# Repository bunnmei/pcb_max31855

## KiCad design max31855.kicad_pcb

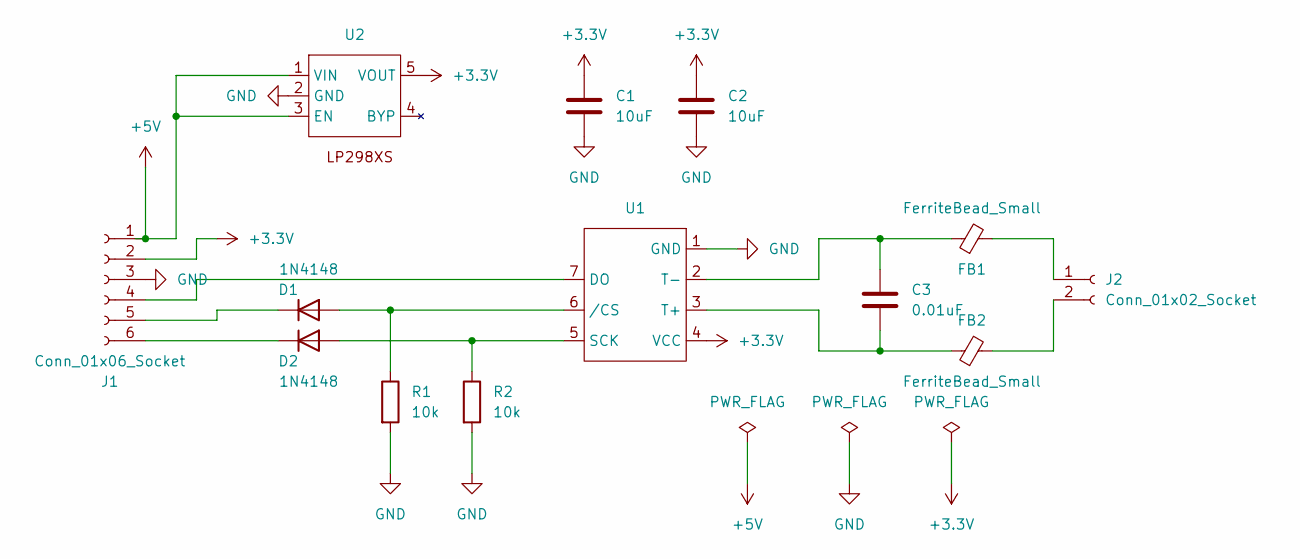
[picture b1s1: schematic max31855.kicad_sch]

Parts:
C1, C2: 10uF; C_0603_1608Metric
C3: 0.01uF; C_0603_1608Metric
D1, D2: 1N4148; D_0603_1608Metric
FB1, FB2: FerriteBead_Small; C_0603_1608Metric
J1: Conn_01x06_Socket; PinSocket_1x06_P2.54mm_Vertical
J2: Conn_01x02_Socket; PinSocket_1x02_P2.00mm_Vertical
R1, R2: 10k; R_0603_1608Metric
U1: SOIC-8_3.9x4.9mm_P1.27mm
U2: LP298XS

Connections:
+3.3V: C1.1, C2.1, J1.2, U1.4 (VCC), U2.5 (VOUT)
+5V: J1.1, U2.1 (VIN), U2.3 (EN)
GND: C1.2, C2.2, J1.3, R1.2, R2.2, U1.1 (GND), U2.2 (GND)
unnamed: D1.2 (A), R1.1, U1.6 (/CS)
unnamed: D1.1 (K), J1.5
unnamed: D2.2 (A), R2.1, U1.5 (SCK)
unnamed: D2.1 (K), J1.6
unnamed: J1.4, U1.7 (DO)
unnamed: FB1.2, J2.1
unnamed: FB2.2, J2.2
unnamed: C3.2, FB2.1, U1.3 (T+)
unnamed: C3.1, FB1.1, U1.2 (T-)

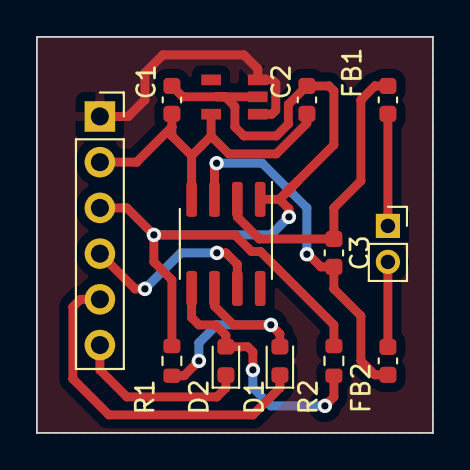
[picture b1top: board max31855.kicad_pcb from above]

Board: 2 copper layers, 22.0 x 22.0 mm, 13 parts (0 on the bottom side), 12 nets.

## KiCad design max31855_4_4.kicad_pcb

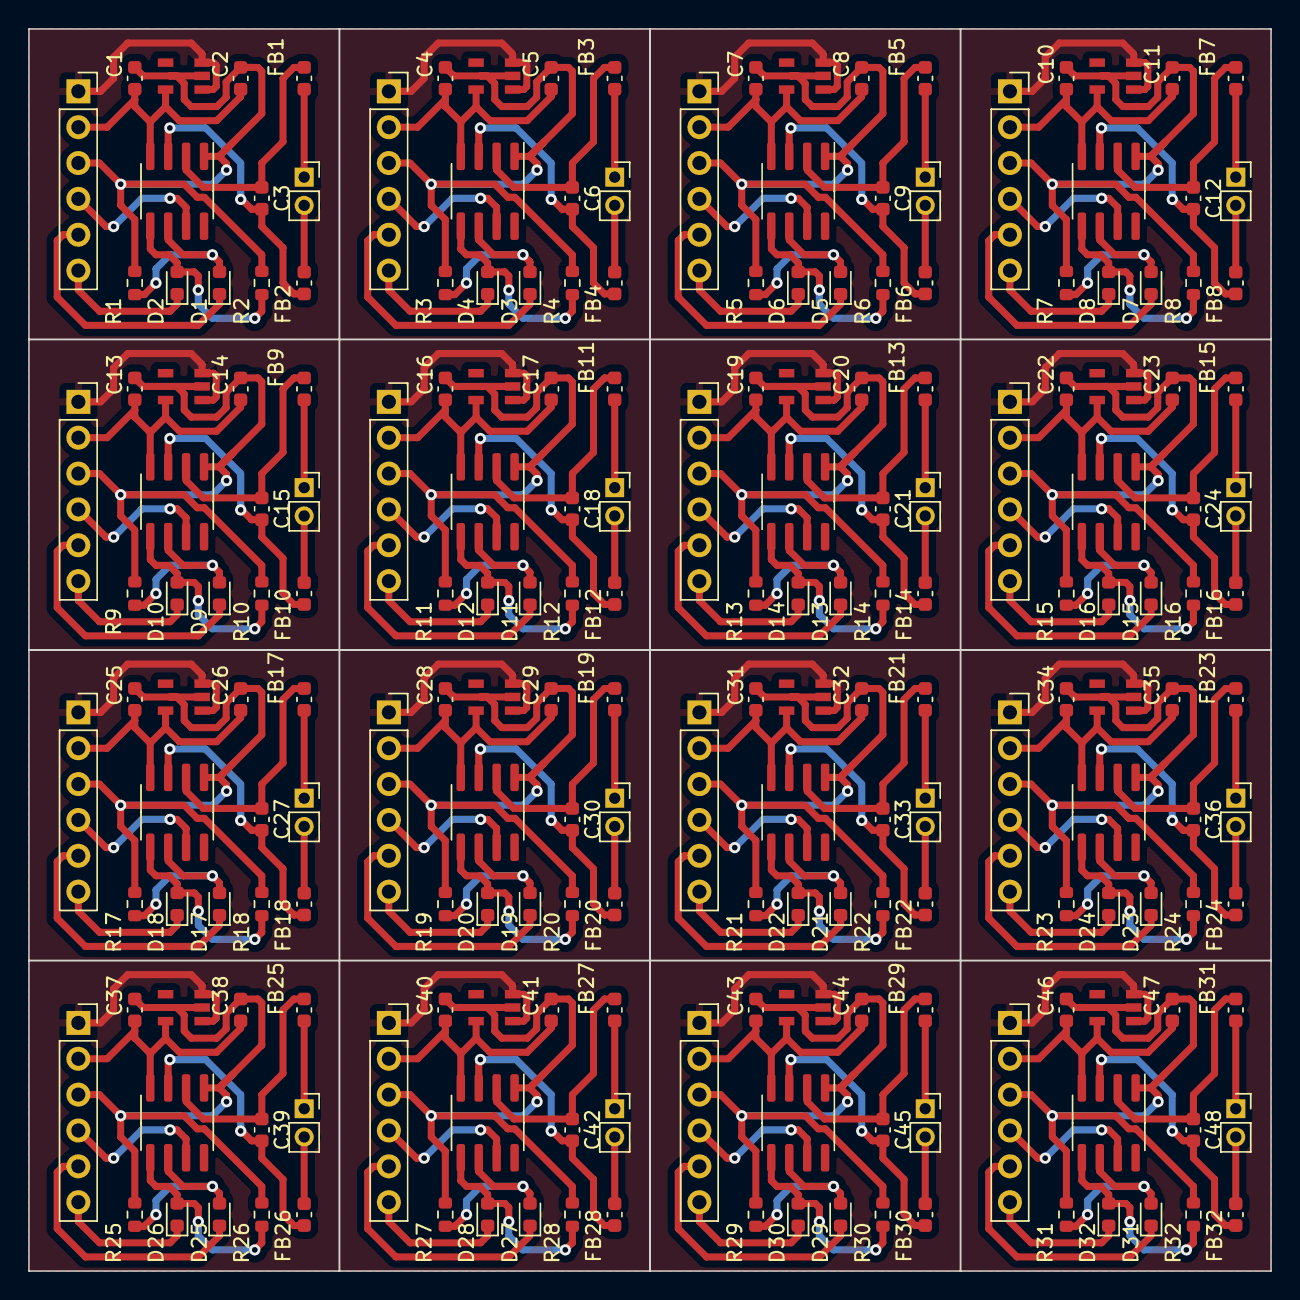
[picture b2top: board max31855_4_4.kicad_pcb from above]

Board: 2 copper layers, 88.0 x 88.0 mm, 208 parts (0 on the bottom side), 12 nets.

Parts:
C1, C2, C4, C5, C7, C8, C10, C11, C13, C14, C16, C17, C19, C20, C22, C23, C25, C26, C28, C29, C31, C32, C34, C35, C37, C38, C40, C41, C43, C44, C46, C47: 10uF; C_0603_1608Metric
C3, C6, C9, C12, C15, C18, C21, C24, C27, C30, C33, C36, C39, C42, C45, C48: 0.01uF; C_0603_1608Metric
D1, D2, D3, D4, D5, D6, D7, D8, D9, D10, D11, D12, D13, D14, D15, D16, D17, D18, D19, D20, D21, D22, D23, D24, D25, D26, D27, D28, D29, D30, D31, D32: 1N4148; D_0603_1608Metric
FB1, FB2, FB3, FB4, FB5, FB6, FB7, FB8, FB9, FB10, FB11, FB12, FB13, FB14, FB15, FB16, FB17, FB18, FB19, FB20, FB21, FB22, FB23, FB24, FB25, FB26, FB27, FB28, FB29, FB30, FB31, FB32: FerriteBead_Small; C_0603_1608Metric
J1, J3, J5, J7, J9, J11, J13, J15, J17, J19, J21, J23, J25, J27, J29, J31: Conn_01x06_Socket; PinSocket_1x06_P2.54mm_Vertical
J2, J4, J6, J8, J10, J12, J14, J16, J18, J20, J22, J24, J26, J28, J30, J32: Conn_01x02_Socket; PinSocket_1x02_P2.00mm_Vertical
R1, R2, R3, R4, R5, R6, R7, R8, R9, R10, R11, R12, R13, R14, R15, R16, R17, R18, R19, R20, R21, R22, R23, R24, R25, R26, R27, R28, R29, R30, R31, R32: 10k; R_0603_1608Metric
U1, U3, U5, U7, U9, U11, U13, U15, U17, U19, U21, U23, U25, U27, U29, U31: SOIC-8_3.9x4.9mm_P1.27mm
U2, U4, U6, U8, U10, U12, U14, U16, U18, U20, U22, U24, U26, U28, U30, U32: LP298XS

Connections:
+3.3V: C1.1, C2.1, C4.1, C5.1, C7.1, C8.1, C10.1, C11.1, C13.1, C14.1, C16.1, C17.1, C19.1, C20.1, C22.1, C23.1, C25.1, C26.1, C28.1, C29.1, C31.1, C32.1, C34.1, C35.1, C37.1, C38.1, C40.1, C41.1, C43.1, C44.1, C46.1, C47.1, J1.2, J3.2, J5.2, J7.2, J9.2, J11.2, J13.2, J15.2, J17.2, J19.2, J21.2, J23.2, J25.2, J27.2, J29.2, J31.2, U1.4 (VCC), U2.5 (VOUT), U3.4 (VCC), U4.5 (VOUT), U5.4 (VCC), U6.5 (VOUT), U7.4 (VCC), U8.5 (VOUT), U9.4 (VCC), U10.5 (VOUT), U11.4 (VCC), U12.5 (VOUT), U13.4 (VCC), U14.5 (VOUT), U15.4 (VCC), U16.5 (VOUT), U17.4 (VCC), U18.5 (VOUT), U19.4 (VCC), U20.5 (VOUT), U21.4 (VCC), U22.5 (VOUT), U23.4 (VCC), U24.5 (VOUT), U25.4 (VCC), U26.5 (VOUT), U27.4 (VCC), U28.5 (VOUT), U29.4 (VCC), U30.5 (VOUT), U31.4 (VCC), U32.5 (VOUT)
+5V: J1.1, J3.1, J5.1, J7.1, J9.1, J11.1, J13.1, J15.1, J17.1, J19.1, J21.1, J23.1, J25.1, J27.1, J29.1, J31.1, U2.1 (VIN), U2.3 (EN), U4.1 (VIN), U4.3 (EN), U6.1 (VIN), U6.3 (EN), U8.1 (VIN), U8.3 (EN), U10.1 (VIN), U10.3 (EN), U12.1 (VIN), U12.3 (EN), U14.1 (VIN), U14.3 (EN), U16.1 (VIN), U16.3 (EN), U18.1 (VIN), U18.3 (EN), U20.1 (VIN), U20.3 (EN), U22.1 (VIN), U22.3 (EN), U24.1 (VIN), U24.3 (EN), U26.1 (VIN), U26.3 (EN), U28.1 (VIN), U28.3 (EN), U30.1 (VIN), U30.3 (EN), U32.1 (VIN), U32.3 (EN)
GND: C1.2, C2.2, C4.2, C5.2, C7.2, C8.2, C10.2, C11.2, C13.2, C14.2, C16.2, C17.2, C19.2, C20.2, C22.2, C23.2, C25.2, C26.2, C28.2, C29.2, C31.2, C32.2, C34.2, C35.2, C37.2, C38.2, C40.2, C41.2, C43.2, C44.2, C46.2, C47.2, J1.3, J3.3, J5.3, J7.3, J9.3, J11.3, J13.3, J15.3, J17.3, J19.3, J21.3, J23.3, J25.3, J27.3, J29.3, J31.3, R1.2, R2.2, R3.2, R4.2, R5.2, R6.2, R7.2, R8.2, R9.2, R10.2, R11.2, R12.2, R13.2, R14.2, R15.2, R16.2, R17.2, R18.2, R19.2, R20.2, R21.2, R22.2, R23.2, R24.2, R25.2, R26.2, R27.2, R28.2, R29.2, R30.2, R31.2, R32.2, U1.1 (GND), U2.2 (GND), U3.1 (GND), U4.2 (GND), U5.1 (GND), U6.2 (GND), U7.1 (GND), U8.2 (GND), U9.1 (GND), U10.2 (GND), U11.1 (GND), U12.2 (GND), U13.1 (GND), U14.2 (GND), U15.1 (GND), U16.2 (GND), U17.1 (GND), U18.2 (GND), U19.1 (GND), U20.2 (GND), U21.1 (GND), U22.2 (GND), U23.1 (GND), U24.2 (GND), U25.1 (GND), U26.2 (GND), U27.1 (GND), U28.2 (GND), U29.1 (GND), U30.2 (GND), U31.1 (GND), U32.2 (GND)
unnamed: D1.2 (A), D3.2 (A), D5.2 (A), D7.2 (A), D9.2 (A), D11.2 (A), D13.2 (A), D15.2 (A), D17.2 (A), D19.2 (A), D21.2 (A), D23.2 (A), D25.2 (A), D27.2 (A), D29.2 (A), D31.2 (A), R1.1, R3.1, R5.1, R7.1, R9.1, R11.1, R13.1, R15.1, R17.1, R19.1, R21.1, R23.1, R25.1, R27.1, R29.1, R31.1, U1.6 (/CS), U3.6 (/CS), U5.6 (/CS), U7.6 (/CS), U9.6 (/CS), U11.6 (/CS), U13.6 (/CS), U15.6 (/CS), U17.6 (/CS), U19.6 (/CS), U21.6 (/CS), U23.6 (/CS), U25.6 (/CS), U27.6 (/CS), U29.6 (/CS), U31.6 (/CS)
unnamed: D1.1 (K), D3.1 (K), D5.1 (K), D7.1 (K), D9.1 (K), D11.1 (K), D13.1 (K), D15.1 (K), D17.1 (K), D19.1 (K), D21.1 (K), D23.1 (K), D25.1 (K), D27.1 (K), D29.1 (K), D31.1 (K), J1.5, J3.5, J5.5, J7.5, J9.5, J11.5, J13.5, J15.5, J17.5, J19.5, J21.5, J23.5, J25.5, J27.5, J29.5, J31.5
unnamed: D2.2 (A), D4.2 (A), D6.2 (A), D8.2 (A), D10.2 (A), D12.2 (A), D14.2 (A), D16.2 (A), D18.2 (A), D20.2 (A), D22.2 (A), D24.2 (A), D26.2 (A), D28.2 (A), D30.2 (A), D32.2 (A), R2.1, R4.1, R6.1, R8.1, R10.1, R12.1, R14.1, R16.1, R18.1, R20.1, R22.1, R24.1, R26.1, R28.1, R30.1, R32.1, U1.5 (SCK), U3.5 (SCK), U5.5 (SCK), U7.5 (SCK), U9.5 (SCK), U11.5 (SCK), U13.5 (SCK), U15.5 (SCK), U17.5 (SCK), U19.5 (SCK), U21.5 (SCK), U23.5 (SCK), U25.5 (SCK), U27.5 (SCK), U29.5 (SCK), U31.5 (SCK)
unnamed: D2.1 (K), D4.1 (K), D6.1 (K), D8.1 (K), D10.1 (K), D12.1 (K), D14.1 (K), D16.1 (K), D18.1 (K), D20.1 (K), D22.1 (K), D24.1 (K), D26.1 (K), D28.1 (K), D30.1 (K), D32.1 (K), J1.6, J3.6, J5.6, J7.6, J9.6, J11.6, J13.6, J15.6, J17.6, J19.6, J21.6, J23.6, J25.6, J27.6, J29.6, J31.6
unnamed: J1.4, J3.4, J5.4, J7.4, J9.4, J11.4, J13.4, J15.4, J17.4, J19.4, J21.4, J23.4, J25.4, J27.4, J29.4, J31.4, U1.7 (DO), U3.7 (DO), U5.7 (DO), U7.7 (DO), U9.7 (DO), U11.7 (DO), U13.7 (DO), U15.7 (DO), U17.7 (DO), U19.7 (DO), U21.7 (DO), U23.7 (DO), U25.7 (DO), U27.7 (DO), U29.7 (DO), U31.7 (DO)
unnamed: FB1.2, FB3.2, FB5.2, FB7.2, FB9.2, FB11.2, FB13.2, FB15.2, FB17.2, FB19.2, FB21.2, FB23.2, FB25.2, FB27.2, FB29.2, FB31.2, J2.1, J4.1, J6.1, J8.1, J10.1, J12.1, J14.1, J16.1, J18.1, J20.1, J22.1, J24.1, J26.1, J28.1, J30.1, J32.1
unnamed: FB2.2, FB4.2, FB6.2, FB8.2, FB10.2, FB12.2, FB14.2, FB16.2, FB18.2, FB20.2, FB22.2, FB24.2, FB26.2, FB28.2, FB30.2, FB32.2, J2.2, J4.2, J6.2, J8.2, J10.2, J12.2, J14.2, J16.2, J18.2, J20.2, J22.2, J24.2, J26.2, J28.2, J30.2, J32.2
unnamed: C3.2, C6.2, C9.2, C12.2, C15.2, C18.2, C21.2, C24.2, C27.2, C30.2, C33.2, C36.2, C39.2, C42.2, C45.2, C48.2, FB2.1, FB4.1, FB6.1, FB8.1, FB10.1, FB12.1, FB14.1, FB16.1, FB18.1, FB20.1, FB22.1, FB24.1, FB26.1, FB28.1, FB30.1, FB32.1, U1.3 (T+), U3.3 (T+), U5.3 (T+), U7.3 (T+), U9.3 (T+), U11.3 (T+), U13.3 (T+), U15.3 (T+), U17.3 (T+), U19.3 (T+), U21.3 (T+), U23.3 (T+), U25.3 (T+), U27.3 (T+), U29.3 (T+), U31.3 (T+)
unnamed: C3.1, C6.1, C9.1, C12.1, C15.1, C18.1, C21.1, C24.1, C27.1, C30.1, C33.1, C36.1, C39.1, C42.1, C45.1, C48.1, FB1.1, FB3.1, FB5.1, FB7.1, FB9.1, FB11.1, FB13.1, FB15.1, FB17.1, FB19.1, FB21.1, FB23.1, FB25.1, FB27.1, FB29.1, FB31.1, U1.2 (T-), U3.2 (T-), U5.2 (T-), U7.2 (T-), U9.2 (T-), U11.2 (T-), U13.2 (T-), U15.2 (T-), U17.2 (T-), U19.2 (T-), U21.2 (T-), U23.2 (T-), U25.2 (T-), U27.2 (T-), U29.2 (T-), U31.2 (T-)
